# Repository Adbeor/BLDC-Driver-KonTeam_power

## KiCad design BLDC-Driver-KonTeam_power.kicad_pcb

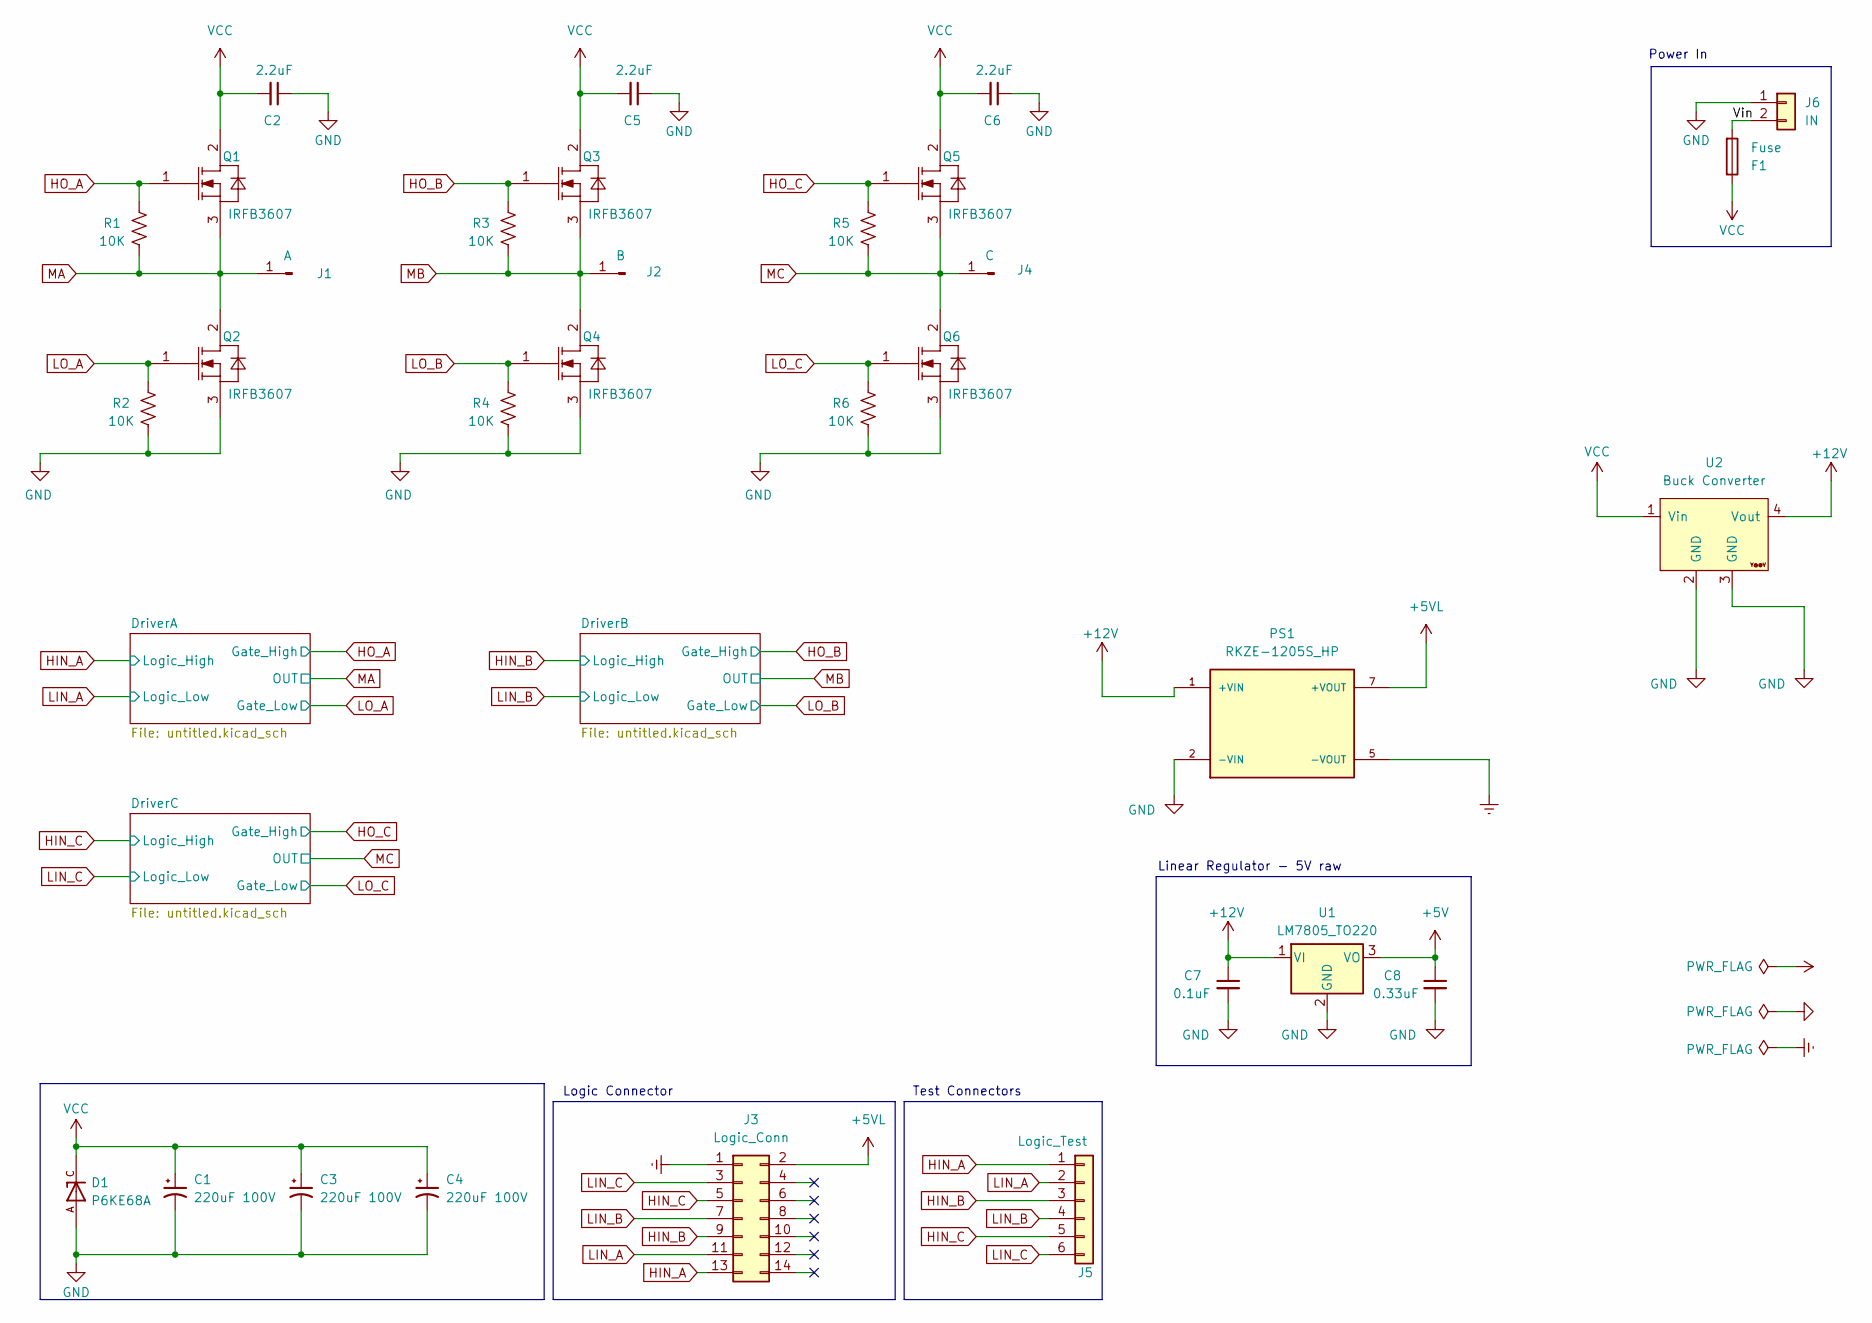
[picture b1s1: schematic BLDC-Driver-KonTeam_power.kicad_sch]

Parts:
C1, C3, C4: 220uF 100V; CP_Radial_D10.0mm_P2.50mm
C2, C5, C6: 2.2uF; C_0805_2012Metric_Pad1.18x1.45mm_HandSolder
C7: 0.1uF; C_Disc_D7.5mm_W2.5mm_P5.00mm
C8: 0.33uF; C_Disc_D7.5mm_W2.5mm_P5.00mm
D1: P6KE68A; DIOAD1300W80L670D310; PARTREV K2105
F1: Fuse; Fuse_Littelfuse-LVR100
J1: A; TestPoint_Loop_D3.80mm_Drill2.0mm
J2: B; TestPoint_Loop_D3.80mm_Drill2.0mm
J3: Logic_Conn; IDC-Header_2x07_P2.54mm_Vertical
J4: C; TestPoint_Loop_D3.80mm_Drill2.0mm
J5: Logic_Test; PinSocket_1x06_P2.54mm_Vertical
J6: IN; AMASS_XT60-F_1x02_P7.20mm_Vertical
PS1: RKZE-1205S_HP; CONV_RKZE-1205S_HP; PARTREV 1
Q1, Q2, Q3, Q4, Q5, Q6: IRFB3607; TO254P1016X419X2286-3; PARTREV 09/21/10
R1, R2, R3, R4, R5, R6: 10K; R_0805_2012Metric_Pad1.20x1.40mm_HandSolder
U1: LM7805_TO220; TO-220-3_Vertical
U2: Buck Converter; DC_DC_LM2596_small

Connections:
+5V: C8.1, U1.3 (VO); also elsewhere on the board
+5VL: J3.2, PS1.7 (+VOUT)
+12V: C7.1, PS1.1 (+VIN), U1.1 (VI), U2.4 (Vout); also elsewhere on the board
/Vin: F1.2, J6.2
Earth: J3.1, PS1.5 (-VOUT); also elsewhere on the board
GND: C1.2, C2.1, C3.2, C4.2, C5.1, C6.1, C7.2, C8.2, D1.A, J6.1, PS1.2 (-VIN), Q2.3 (SOURCE), Q4.3 (SOURCE), Q6.3 (SOURCE), R2.1, R4.1, R6.1, U1.2 (GND), U2.2 (GND), U2.3 (GND); also elsewhere on the board
HIN_A: J3.13, J5.1; also elsewhere on the board
HIN_B: J3.9, J5.3; also elsewhere on the board
HIN_C: J3.5, J5.5; also elsewhere on the board
HO_A: Q1.1 (GATE), R1.2; also elsewhere on the board
HO_B: Q3.1 (GATE), R3.2; also elsewhere on the board
HO_C: Q5.1 (GATE), R5.2; also elsewhere on the board
LIN_A: J3.11, J5.2; also elsewhere on the board
LIN_B: J3.7, J5.4; also elsewhere on the board
LIN_C: J3.3, J5.6; also elsewhere on the board
LO_A: Q2.1 (GATE), R2.2; also elsewhere on the board
LO_B: Q4.1 (GATE), R4.2; also elsewhere on the board
LO_C: Q6.1 (GATE), R6.2; also elsewhere on the board
MA: J1.1, Q1.3 (SOURCE), Q2.2 (DRAIN), R1.1; also elsewhere on the board
MB: J2.1, Q3.3 (SOURCE), Q4.2 (DRAIN), R3.1; also elsewhere on the board
MC: J4.1, Q5.3 (SOURCE), Q6.2 (DRAIN), R5.1; also elsewhere on the board
VCC: C1.1, C2.2, C3.1, C4.1, C5.2, C6.2, D1.C, F1.1, Q1.2 (DRAIN), Q3.2 (DRAIN), Q5.2 (DRAIN), U2.1 (Vin)

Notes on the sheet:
Linear Regulator - 5V raw
Logic Connector
Test Connectors
Power In

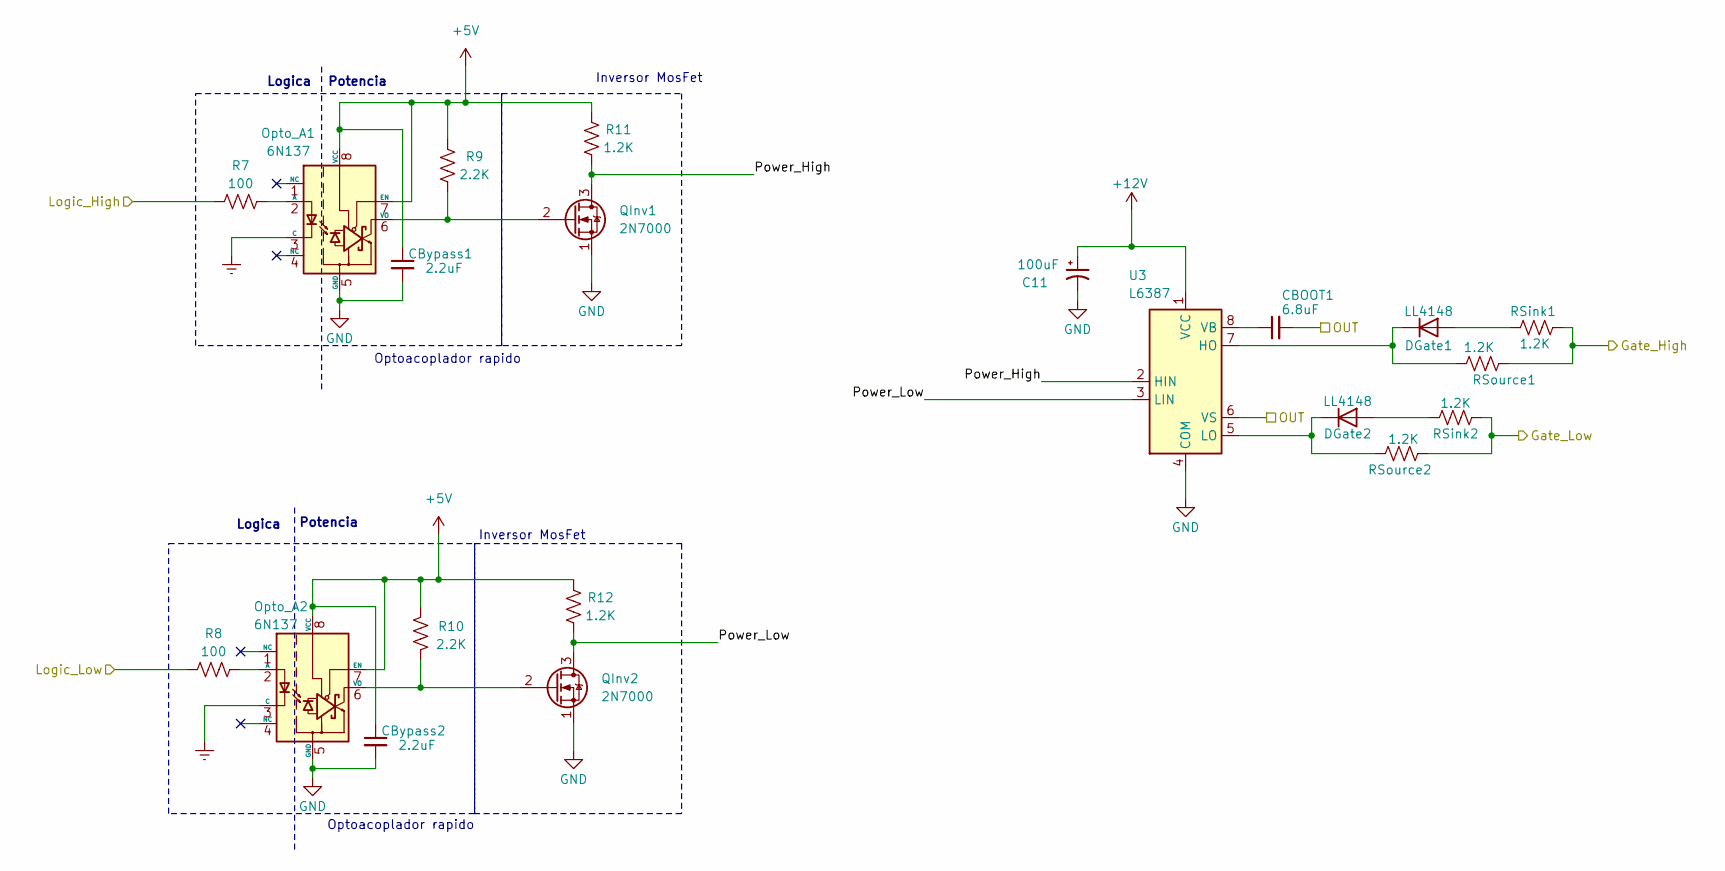
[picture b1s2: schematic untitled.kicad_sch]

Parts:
C11: 100uF; C_0805_2012Metric_Pad1.18x1.45mm_HandSolder
CBOOT1: 6.8uF; C_0805_2012Metric_Pad1.18x1.45mm_HandSolder
CBypass1, CBypass2: 2.2uF; C_0805_2012Metric_Pad1.18x1.45mm_HandSolder
DGate1, DGate2: LL4148; D_MiniMELF_Handsoldering
Opto_A1, Opto_A2: 6N137; DIP-8_W7.62mm
QInv1, QInv2: 2N7000; TO-92_Inline
R7, R8: 100; R_0805_2012Metric_Pad1.20x1.40mm_HandSolder
R9, R10: 2.2K; R_0805_2012Metric_Pad1.20x1.40mm_HandSolder
R11, R12: 1.2K; R_0805_2012Metric_Pad1.20x1.40mm_HandSolder
RSink1, RSink2: 1.2K; R_0805_2012Metric_Pad1.20x1.40mm_HandSolder
RSource1, RSource2: 1.2K; R_0805_2012Metric_Pad1.20x1.40mm_HandSolder
U3: L6387; SOIC127P600X175-8N

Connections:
+5V: CBypass1.1, CBypass2.1, Opto_A1.7 (EN), Opto_A1.8 (VCC), Opto_A2.7 (EN), Opto_A2.8 (VCC), R9.1, R10.1, R11.1, R12.1; also elsewhere on the board
+12V: C11.1, U3.1 (VCC); also elsewhere on the board
/DriverA/Power_High: QInv1.3 (D), R11.2, U3.2 (HIN)
/DriverA/Power_Low: QInv2.3 (D), R12.2, U3.3 (LIN)
Earth: Opto_A1.3 (C), Opto_A2.3 (C); also elsewhere on the board
GND: C11.2, CBypass1.2, CBypass2.2, Opto_A1.5 (GND), Opto_A2.5 (GND), QInv1.1 (S), QInv2.1 (S), U3.4 (COM); also elsewhere on the board
HIN_A: R7.1; also elsewhere on the board
HO_A: RSink1.2, RSource1.2; also elsewhere on the board
LIN_A: R8.1; also elsewhere on the board
LO_A: RSink2.2, RSource2.2; also elsewhere on the board
MA: CBOOT1.2, U3.6 (VS); also elsewhere on the board
unnamed: DGate1.2 (A), RSink1.1
unnamed: DGate1.1 (K), RSource1.1, U3.7 (HO)
unnamed: DGate2.2 (A), RSink2.1
unnamed: DGate2.1 (K), RSource2.1, U3.5 (LO)
unnamed: Opto_A1.2 (A), R7.2
unnamed: Opto_A1.6 (VO), QInv1.2 (G), R9.2
unnamed: Opto_A2.2 (A), R8.2
unnamed: Opto_A2.6 (VO), QInv2.2 (G), R10.2
unnamed: CBOOT1.1, U3.8 (VB)

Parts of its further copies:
C14, C17: 100uF; C_0805_2012Metric_Pad1.18x1.45mm_HandSolder
CBOOT2, CBOOT3: 6.8uF; C_0805_2012Metric_Pad1.18x1.45mm_HandSolder
CBypass3, CBypass4, CBypass5, CBypass6: 2.2uF; C_0805_2012Metric_Pad1.18x1.45mm_HandSolder
DGate3, DGate4, DGate5, DGate6: LL4148; D_MiniMELF_Handsoldering
Opto_B1, Opto_B2: 6N137; DIP-8_W7.62mm
Opto_C1, Opto_C2: 6N137; DIP-8_W7.62mm
QInv3, QInv4, QInv5, QInv6: 2N7000; TO-92_Inline
R17, R18, R27, R28: 100; R_0805_2012Metric_Pad1.20x1.40mm_HandSolder
R19, R20, R29, R30: 2.2K; R_0805_2012Metric_Pad1.20x1.40mm_HandSolder
R21, R22, R31, R32: 1.2K; R_0805_2012Metric_Pad1.20x1.40mm_HandSolder
RSink3, RSink4, RSink5, RSink6: 1.2K; R_0805_2012Metric_Pad1.20x1.40mm_HandSolder
RSource3, RSource4, RSource5, RSource6: 1.2K; R_0805_2012Metric_Pad1.20x1.40mm_HandSolder
U4, U5: L6387; SOIC127P600X175-8N

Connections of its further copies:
+5V: CBypass3.1, CBypass4.1, CBypass5.1, CBypass6.1, Opto_B1.7 (EN), Opto_B1.8 (VCC), Opto_B2.7 (EN), Opto_B2.8 (VCC), Opto_C1.7 (EN), Opto_C1.8 (VCC), Opto_C2.7 (EN), Opto_C2.8 (VCC), R19.1, R20.1, R21.1, R22.1, R29.1, R30.1, R31.1, R32.1; also elsewhere on the board
+12V: C14.1, C17.1, U4.1 (VCC), U5.1 (VCC); also elsewhere on the board
/DriverB/Power_High: QInv3.3 (D), R21.2, U4.2 (HIN)
/DriverB/Power_Low: QInv4.3 (D), R22.2, U4.3 (LIN)
/DriverC/Power_High: QInv5.3 (D), R31.2, U5.2 (HIN)
/DriverC/Power_Low: QInv6.3 (D), R32.2, U5.3 (LIN)
Earth: Opto_B1.3 (C), Opto_B2.3 (C), Opto_C1.3 (C), Opto_C2.3 (C); also elsewhere on the board
GND: C14.2, C17.2, CBypass3.2, CBypass4.2, CBypass5.2, CBypass6.2, Opto_B1.5 (GND), Opto_B2.5 (GND), Opto_C1.5 (GND), Opto_C2.5 (GND), QInv3.1 (S), QInv4.1 (S), QInv5.1 (S), QInv6.1 (S), U4.4 (COM), U5.4 (COM); also elsewhere on the board
HIN_B: R17.1; also elsewhere on the board
HIN_C: R27.1; also elsewhere on the board
HO_B: RSink3.2, RSource3.2; also elsewhere on the board
HO_C: RSink5.2, RSource5.2; also elsewhere on the board
LIN_B: R18.1; also elsewhere on the board
LIN_C: R28.1; also elsewhere on the board
LO_B: RSink4.2, RSource4.2; also elsewhere on the board
LO_C: RSink6.2, RSource6.2; also elsewhere on the board
MB: CBOOT2.2, U4.6 (VS); also elsewhere on the board
MC: CBOOT3.2, U5.6 (VS); also elsewhere on the board
unnamed: DGate3.2 (A), RSink3.1
unnamed: DGate3.1 (K), RSource3.1, U4.7 (HO)
unnamed: DGate4.2 (A), RSink4.1
unnamed: DGate4.1 (K), RSource4.1, U4.5 (LO)
unnamed: DGate5.2 (A), RSink5.1
unnamed: DGate5.1 (K), RSource5.1, U5.7 (HO)
unnamed: DGate6.2 (A), RSink6.1
unnamed: DGate6.1 (K), RSource6.1, U5.5 (LO)
unnamed: Opto_B1.2 (A), R17.2
unnamed: Opto_B1.6 (VO), QInv3.2 (G), R19.2
unnamed: Opto_B2.2 (A), R18.2
unnamed: Opto_B2.6 (VO), QInv4.2 (G), R20.2
unnamed: Opto_C1.2 (A), R27.2
unnamed: Opto_C1.6 (VO), QInv5.2 (G), R29.2
unnamed: Opto_C2.2 (A), R28.2
unnamed: Opto_C2.6 (VO), QInv6.2 (G), R30.2
unnamed: CBOOT2.1, U4.8 (VB)
unnamed: CBOOT3.1, U5.8 (VB)

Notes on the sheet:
Inversor MosFet
Potencia
Optoacoplador rapido
Logica

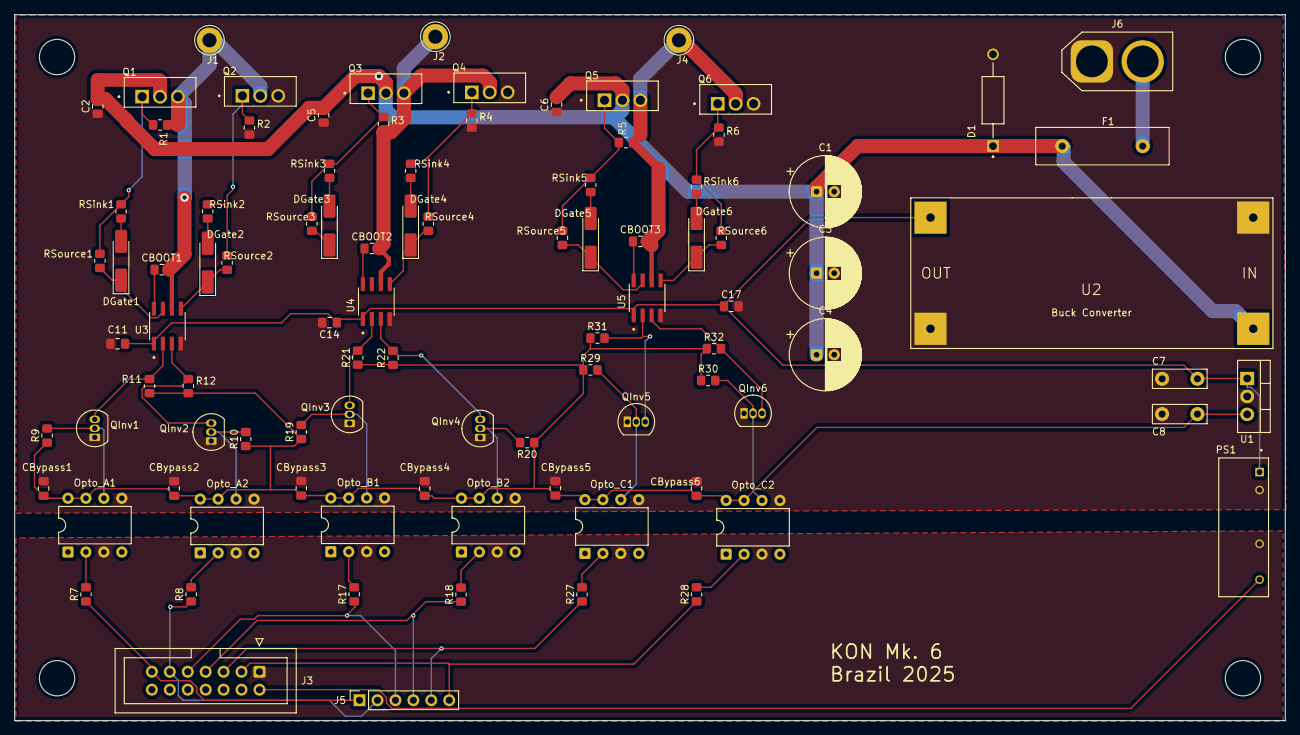
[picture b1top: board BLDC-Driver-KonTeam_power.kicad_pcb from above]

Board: 2 copper layers, 180.0 x 100.0 mm, 94 parts (0 on the bottom side), 55 nets.

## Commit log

2025-06-08 Inicial
2025-06-08 Formato Gate Drivers Enable
2025-06-08 Refactoring the layout or the pcb. Delete the test points for the mosfet's gates , use the gate enable jumpers instead. layout of IR2021 drivers now has separated the power and the logic phases to en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
    Todo:
    - Investigate about the fly back diode efficency in the new mosfet
    - Get calculation for the ripple supresion for the buck converter.
    - remake the footprint of the buck converter.
    - add the TVS diode to
2025-06-15 - Added Footprint Buck converter - Add TVS diode for over voltage protection - Routed tracks (need confirmation) - Add conector for the horn, need to add specific connector - Added .step format for t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
    Todo:
    - add holes to fix to the car structure
    - Make specific connector for the horn
    - Calculate heatsink spacing
    - Investigate about RC snubbers
    - Investigate about the fly back diode efficency in the new mosfet
2026-02-25 cambio de driver, cambio de mosfet , añadido aislamiento galvanico entre logica y potencia
2026-02-26 posicion de las resistencias de gate corregidas
2026-02-26 correciones( aislamiento LM7805) , cambio de ID , primer ruteo
